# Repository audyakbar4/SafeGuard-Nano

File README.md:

# 🌱 MoodPot — *"Happy Plant, Happy You."*

[Baca dalam Bahasa Indonesia](README.md) | [🌐 Read in English](README_EN.md)

---

## 🎬 Commercial Video

## Read The Book Now

## 🎬 Demo Video Project

##  Overview

🌱 MoodPot – Ketika Tanaman Bisa Bercerita Lewat Ekspresi

Pernah merasa bersalah karena lupa menyiram tanaman? Atau bingung kapan waktunya menyiram? MoodPot hadir sebagai sahabat tanaman yang bisa berbicara padamu lewat ekspresi wajah.

Bayangkan kamu pulang ke rumah setelah hari yang melelahkan. Di pojok ruangan, tanaman kesayanganmu sedang “menatap” dengan wajah sedih. Bukan karena marah—tapi karena ia haus. Tapi tenang, MoodPot sudah tahu apa yang harus dilakukan. Ia otomatis menyalakan pompa kecil dan memberi tanamanmu minuman yang dibutuhkannya.

Beberapa saat kemudian, wajahnya berubah ceria. Tanahnya lembap kembali, dan tanamanmu pun bahagia.

MoodPot bukan sekadar pot bunga. Ia adalah teman kecil yang mengingatkan kita bahwa merawat tanaman bisa menjadi pengalaman yang menyenangkan, komunikatif, dan penuh empati—bahkan untuk pemula sekalipun. Dengan sensor kelembapan tanah, ekspresi LED Matrix yang menggemaskan, dan sistem penyiraman otomatis, MoodPot menjadikan setiap interaksi kecil terasa berarti.

Karena tanaman juga punya cara untuk menyampaikan perasaannya—dan MoodPot menerjemahkannya untukmu.

---

## 🎯 Objectives

- 🔍 Mendeteksi kelembapan tanah secara otomatis menggunakan sensor.
- 😊 Memberikan feedback visual (wajah senang/datar/sedih) melalui LED Matrix.
- 💧 Menyiram tanaman secara otomatis ketika tanah kering.
- 💻 Menyediakan monitoring kelembapan secara real-time melalui UART ke komputer.

---

## 🧠 Background

Merawat tanaman sering kali menjadi tantangan, terutama bagi orang-orang sibuk atau yang belum terbiasa dengan kebutuhan dasar tanaman. Salah satu penyebab tanaman layu adalah kurangnya perhatian terhadap kelembapan tanah.

**MoodPot** memberikan solusi dengan menampilkan *"mood"* tanaman—apakah bahagia, cukup, atau sedih—berdasarkan kondisi tanah, membuat pengguna lebih peduli dan terlibat.

---

## 🖼️ Preview Presentasi

> Klik tombol di atas untuk membuka presentasi secara penuh di Canva.

---

## 🧾 Daftar Isi Presentasi

1. Latar Belakang & Masalah
2. Konsep MoodPot
3. Komponen yang Digunakan
4. Diagram Sistem
5. Demo & Visualisasi
6. Manfaat dan Pengembangan

---

## 🔧 Hardware Components

| Komponen              | Fungsi                                |
|----------------------|----------------------------------------|
| 🧠 Arduino Nano          | Pengontrol utama                      |
| 🌱 Sensor Kelembapan    | Membaca kadar air tanah               |
| 😃 LED Matrix (MAX7219) | Menampilkan ekspresi wajah            |
| 🔌 Relay Module         | Mengendalikan pompa                   |
| 💦 Pompa DC 5V         | Menyiram tanaman otomatis             |
| 🔋 Baterai 18650 2S        | Sumber daya portabel                  |

---

## 💻 Software Tools

- [Arduino IDE](https://www.arduino.cc/en/software)
- [KiCad](https://kicad.org/)
- [Figma](https://www.figma.com/)
- [TinkerCAD](https://www.tinkercad.com/)
- [Thingiverse](https://www.thingiverse.com/)
- [Visual Studio Code](https://code.visualstudio.com/)

---

## 🧭 System Diagram

## Schematic

## Layout

## 3D PCB

## Tampak Dalam

---

## 💡 Simulasi Proyek

🔗 **Tautan Proyek Wokwi**  
[https://wokwi.com/projects/431816390638291969](https://wokwi.com/projects/431903301521434625)

📁 **Dokumentasi Proyek (Google Drive)**  
[https://drive.google.com/drive/folders/1GqONTiI6WEsIznY9d5Q_FcgnjMObSm_b?usp=drive_link](https://drive.google.com/drive/folders/1GqONTiI6WEsIznY9d5Q_FcgnjMObSm_b?usp=drive_link)

## 📄 Desain 3D

📁 **Tutorial Desain 3D (Google Drive)**

[👉 Klik di sini untuk membuka folder Google Drive](https://drive.google.com/drive/folders/1GnPXin400DgNMjtPwBu-FTDF2DJWISpB?usp=drive_link)

🔗 **Desain 3D Vol 1**  
https://www.thingiverse.com/thing:7030558

🔗 **Desain 3D Vol 2**  
https://www.thingiverse.com/thing:7048423

🔗 **Desain 3D Vol **  
https://www.thingiverse.com/thing:7050436

---

## ⚙️ Working Principle

### 🔍 Pembacaan Kelembapan
- Sensor kelembapan tanah mengirim sinyal analog ke Arduino.
- Nilai tinggi → tanah kering; nilai rendah → tanah basah.

### 🧠 Pemrosesan oleh Arduino
- Arduino membaca sensor secara berkala dan membandingkan dengan nilai *threshold*.
- Keputusan diambil untuk menyiram atau tidak.

### 😃 Feedback Visual
- Tanah basah  → LED Matrix menampilkan wajah senang 😊
- Tanah Sedang → LED Matrix menampilkan wajah Datar  😑
- Tanah kering → LED Matrix menampilkan wajah sedih  😢

### 💧 Penyiraman Otomatis
- Jika tanah kering, relay mengaktifkan pompa air.
- Setelah tanah cukup lembap, pompa dimatikan otomatis.

---
## 🚀 Quick Start

MoodPot dikirim dalam kondisi siap pakai (plug and play). Berikut langkah cepat untuk langsung menggunakannya:

### 🪴 Langkah Penggunaan MoodPot:

1. **Isi Tangki Air**
   - siapkan wadah untuk tangki air, isi wadah air hingga penuh kemudian masukkan dc pump / pompa air kedalam wadah yang sudah terisi dengan air.

2. **Colokkan Power**
   - Sambungkan MoodPot ke sumber daya menggunakan kabel USB atau baterai 2S 18650 bawaan.

3. **Tancapkan Sensor ke Tanah**
   - Pastikan sensor kelembapan sudah tertancap di dalam tanah pada pot tanaman kamu.

4. **Lihat Ekspresi Wajah**
   - MoodPot akan langsung menyala dan menampilkan ekspresi wajah:
     - 😊 Bahagia → Tanah lembap, tidak perlu disiram
     - 😐 Netral → Tanah mulai mengering, bersiap menyiram
     - 😢 Sedih → Tanah kering, pompa menyiram otomatis

5. **Selesai**
   - MoodPot akan bekerja otomatis 24/7 tanpa perlu pengaturan manual.

> 💡 Tips: Periksa tangki air setiap beberapa hari agar tidak kehabisan air.

---

## 👨‍💻 Team — Drasoul.Tech

| NRP         | Nama Lengkap                    | Tanggung Jawab               |
|-------------|----------------------------------|------------------------------|
| 2123500003  | Audy Putra Pratama Akbar        | UI/UX Designer               |
| 2123500007  | Muhammad Faizulhaq R            | Hardware                     |
| 2123500010  | Zanuar Rachmat Yusril B.P.      | 3D Designer                  |
| 2123500014  | Ahmad Hafidz Iswananda S        | Project Manager / Hardware  |
| 2123500027  | Ingka Fitra Oemardi             | Programmer                   |

---
## 🌍 Showcase 

- 📢 Dipresentasikan di **PENS Workshop Mikrokontroler 2025**
- 🌟 Ditampilkan dalam demo terbuka oleh dosen pembimbing
- 👨‍🏫 Mendapat feedback positif dari pengajar dan rekan sejawat

📸 Dokumentasi Kegiatan:
[👉 Klik di sini untuk melihat dokumentasi](https://drive.google.com/drive/folders/1GqONTiI6WEsIznY9d5Q_FcgnjMObSm_b?usp=drive_link)

---

## 🎓 Supported by

- 👨‍🏫 Dosen Pengampu: Akhmad Hendriawan, S.T., M.T.
- 📚 Mata Kuliah: Workshop Mikrokontroler
- 🏫 Institusi: Politeknik Elektronika Negeri Surabaya (PENS)
- 🧑‍🔧 Program Studi: Teknik Elektronika

---

## ✅ Future Improvements

- [ ] Tambahkan koneksi Bluetooth untuk kontrol dari HP
- [ ] Implementasi OLED display untuk info lebih lengkap
- [ ] Desain casing 3D cetak

---

## 📄 License

This project is licensed under the MIT License — see the [LICENSE](./LICENSE) file for details.

---

## 🙏 Credits

Developed with 💚 by **Drasoul.Tech**  
A project to bring life, tech, and plants together 🌿

## 📫 Contact Information

For inquiries related to this project — including collaborations, technical questions, or professional opportunities — feel free to reach out via email:

**📧 Email:** [yourname@example.com](mailto:yourname@example.com)

I aim to respond within 1–2 business days. Please include the project name in your subject line for faster reference.

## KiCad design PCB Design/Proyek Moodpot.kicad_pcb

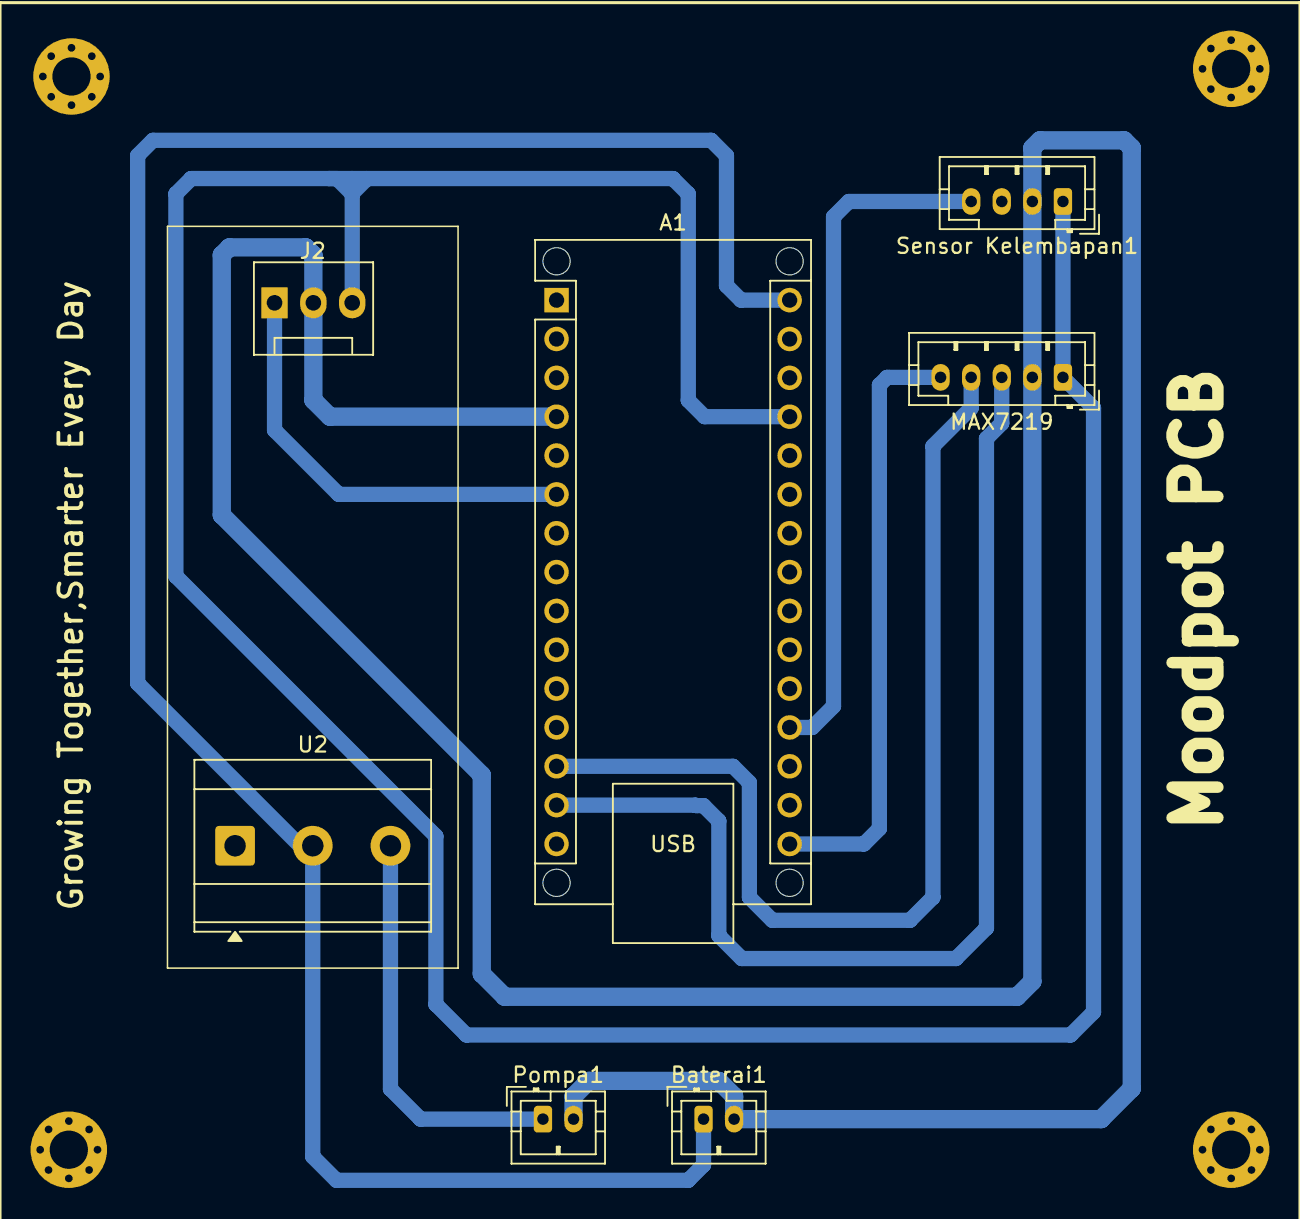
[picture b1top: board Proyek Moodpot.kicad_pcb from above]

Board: 2 copper layers, 7 parts (0 on the bottom side), 9 nets.

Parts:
A1: Arduino_Nano_v3.x; Arduino_Nano_WithMountingHoles
Baterai1: JST_PH_B2B-PH-K_1x02_P2.00mm_Vertical
J2: Conn_01x03_Pin; FanPinHeader_1x03_P2.54mm_Vertical
MAX7219: Conn_01x05_Pin; JST_PH_B5B-PH-K_1x05_P2.00mm_Vertical
Pompa1: JST_PH_B2B-PH-K_1x02_P2.00mm_Vertical
Sensor Kelembapan1: JST_PH_B4B-PH-K_1x04_P2.00mm_Vertical
U2: Screw_Terminal_01x03; TerminalBlock_MetzConnect_Type073_RT02603HBLU_1x03_P5.08mm_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

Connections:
A0: A1.19 (A0), Sensor Kelembapan1.4
CLK: A1.16 (D13), MAX7219.5
CS: A1.13 (D10), MAX7219.4
D3: A1.6 (D3), J2.1
DIN: A1.14 (D11), MAX7219.3
GND: A1.4 (GND), Baterai1.2, J2.2, MAX7219.2, Pompa1.2, Sensor Kelembapan1.2
RELAY_OUT: Pompa1.1, U2.3
VBATT: A1.30 (VIN), Baterai1.1, U2.2
VCC: A1.27 (+5V), J2.3, MAX7219.1, Sensor Kelembapan1.1

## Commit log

2025-04-22 Create Brand
2025-04-23 Create UI-UX Design
2025-04-23 Create User Interface
2025-04-26 Create Design
2025-04-26 Blok Diagram Sistem
2025-04-26 Create software
2025-04-27 Create Pot Kotak
2025-04-27 File Kosongan
2025-04-27 Dikosongkan
2025-04-27 Create face
2025-04-27 mengubah nama
2025-04-27 Rename brandinglogo.jpg to Assets/brandinglogo.jpg
2025-04-28 Update Program
2025-05-12 Create desain pcb
2025-05-14 Create pcb
2025-05-14 Create File
2025-05-18 Rename Screenshot 2025-05-16 211504.png to Schematic.png
2025-05-18 Rename Screenshot 2025-05-16 211519.png to Layout.png
2025-05-18 Rename Screenshot 2025-05-16 213700.png to 3D Viewer PCB.png
2025-05-19 Create pot
2025-05-25 Create This
2025-05-25 Create Future
2025-05-25 Create Ini
2025-06-06 Rename PCB Design/WhatsApp Image 2025-06-02 at 11.42.02_abeca7d9.jpg to Tampilan Dalamjpg
2025-06-06 Rename Tampilan Dalamjpg to PCB Design/Tampilan Dalam.jpg
2025-06-06 Rename WhatsApp Image 2025-06-02 at 11.42.03_0c3cbe79.jpg to Tampak Luar.jpg
2025-06-06 Rename Lucid_Realism_A_clean_and_modern_book_cover_design_showing_a_f_3.jpg to coverbook.jpg
